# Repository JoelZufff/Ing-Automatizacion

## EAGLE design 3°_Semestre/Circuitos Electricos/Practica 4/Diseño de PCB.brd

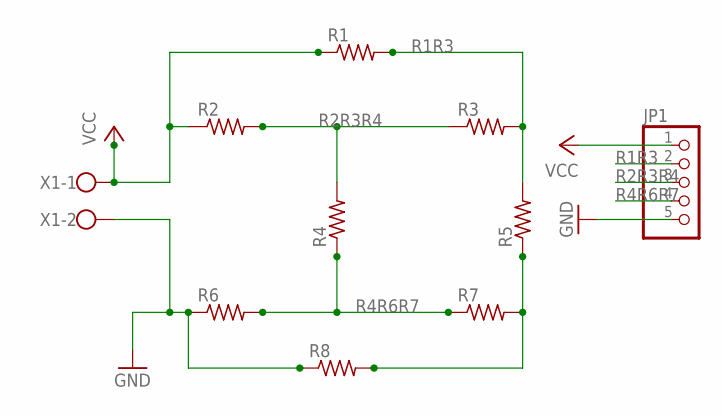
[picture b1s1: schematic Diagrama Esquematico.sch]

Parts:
JP1: PINHD-1X5; 1X05
R1, R2, R3, R4, R5, R6, R7, R8: R-US_0207/10; 0207/10
X1: W237-102

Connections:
GND: JP1.5, R6.1, R8.1, X1.2
unnamed: R5.1, R7.2, R8.2
R1R3: JP1.2, R1.2, R3.2, R5.2
R2R3R4: JP1.3, R2.2, R3.1, R4.2
R4R6R7: JP1.4, R4.1, R6.2, R7.1
VCC: JP1.1, R1.1, R2.1, X1.1

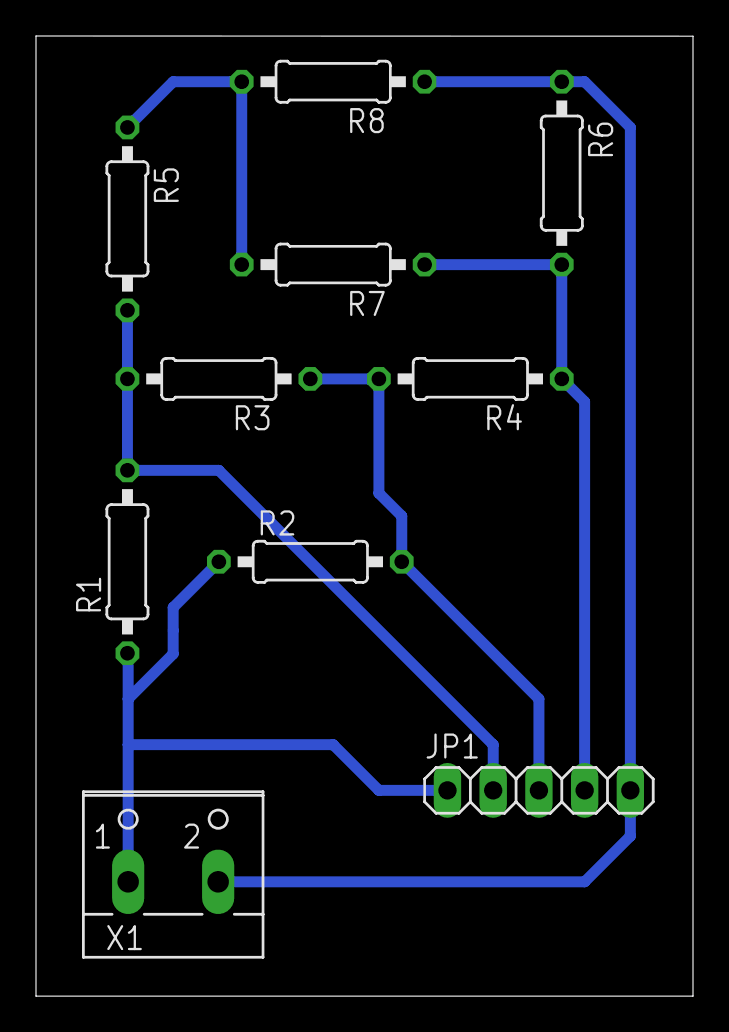
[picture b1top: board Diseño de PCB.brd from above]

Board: 2 copper layers, 36.5 x 53.3 mm, 10 parts (0 on the bottom side), 6 nets.

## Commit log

2024-02-12 Agregue archivos de clases
2024-02-13 Practica 3: Sensor Ultrasonico y Displays
2024-02-17 Practica 4: Cree PWM con control de Duty Cicle con timer 0
2024-02-18 Practica 4: Configure ADC e hize macro para facilitar lectura
2024-02-18 Practica 4: Agregue los procesos al ciclo infinito y arregle problemas a funcion display
2024-02-18 Agregue tareas de semestre pasado
2024-02-18 Practica 4: Agregue LED de acoplamiento y corregi errores
2024-02-19 Agregue compilacion con task de vs code y librerias
2024-02-25 Practica 4: Version Final del codigo
2024-02-27 Practica 4: Version Final
2024-03-02 Practica 5: Recibimos caracteres de puerto serial a 9600 baudios
2024-03-05 Practica 5: Protipo de transmision
2024-03-05 Practica 5: Version Final
2024-03-12 Practica 6: GPS version final
2024-03-21 Practica 7: Impresion en GLCD
2024-03-21 Practica 7: Elementos e impresion
2024-03-24 Practica 7: Videojuego version final
2024-06-18 SCADA: Inicio y avance de programacion
2024-06-18 Scada: Prueba PID
2024-06-21 SCADA: Version final
2024-08-12 Reorganizacion de carpetas
2024-08-17 Sistemas digitales: Practica 1
2024-08-18 Diseño CAD: Tarea 1-10
2024-08-22 Actualizacion de practicas y clases de automatizacion
2024-09-10 Actualizacion 5o semestre
2024-09-17 Sistemas Digitales: Practica_5
2024-09-28 Actualizacion de nombres y practicas
2024-09-28 Sistemas digitales: Practica 6
2024-10-06 Sistemas Digitales I: Practica 7 - LCD
2024-10-09 Automatizacion: Circuitos neumaticos oscilantes con temporizador
2024-10-16 Organizacion de archivos y Examen 2 Automatizacion
2024-10-17 Sistemas Digitales I: Avances practica 9
2024-11-05 Automatizacion I: Examen 3
2024-11-12 Sistemas Digitales I: Practica 10 - Motor a pasos
2024-11-18 Sistemas Digitales I: Practica 11 - DAC
2024-11-19 Diseño de sistemas electricos: Proyecto de instalacion electrica de Centro de computo
2024-11-26 Automatizacion I: Sistema neumatico clasificador de cajas por color
2024-11-28 Automatizacion I: Entrega final
2024-12-11 Actualizacion de fin de 5to semestre
2025-01-15 FIN de 5o semestre
2025-03-21 Actualizacion de 6o semestre
2025-04-07 Actualizacion Balancin
2025-04-07 Actualizacion PISDRSL
2025-05-03 Avance de tesis PISDRSL
2025-05-03 mend
2025-05-09 Avance codigo PISDRSL
2025-05-10 Tesis PISDRSL: TCP server funcional
2025-05-11 Tesis PISDRSL: Ya funciona TCRT5000 y MPU6050
2025-05-14 Tesis PISDRSL: Avance a sistema de control
2025-05-15 Tesis PISDRSL: Mejora de organizacion y de codigo y avance en interfaz grafica
2025-05-17 Tesis PISDRSL: Mejoras
